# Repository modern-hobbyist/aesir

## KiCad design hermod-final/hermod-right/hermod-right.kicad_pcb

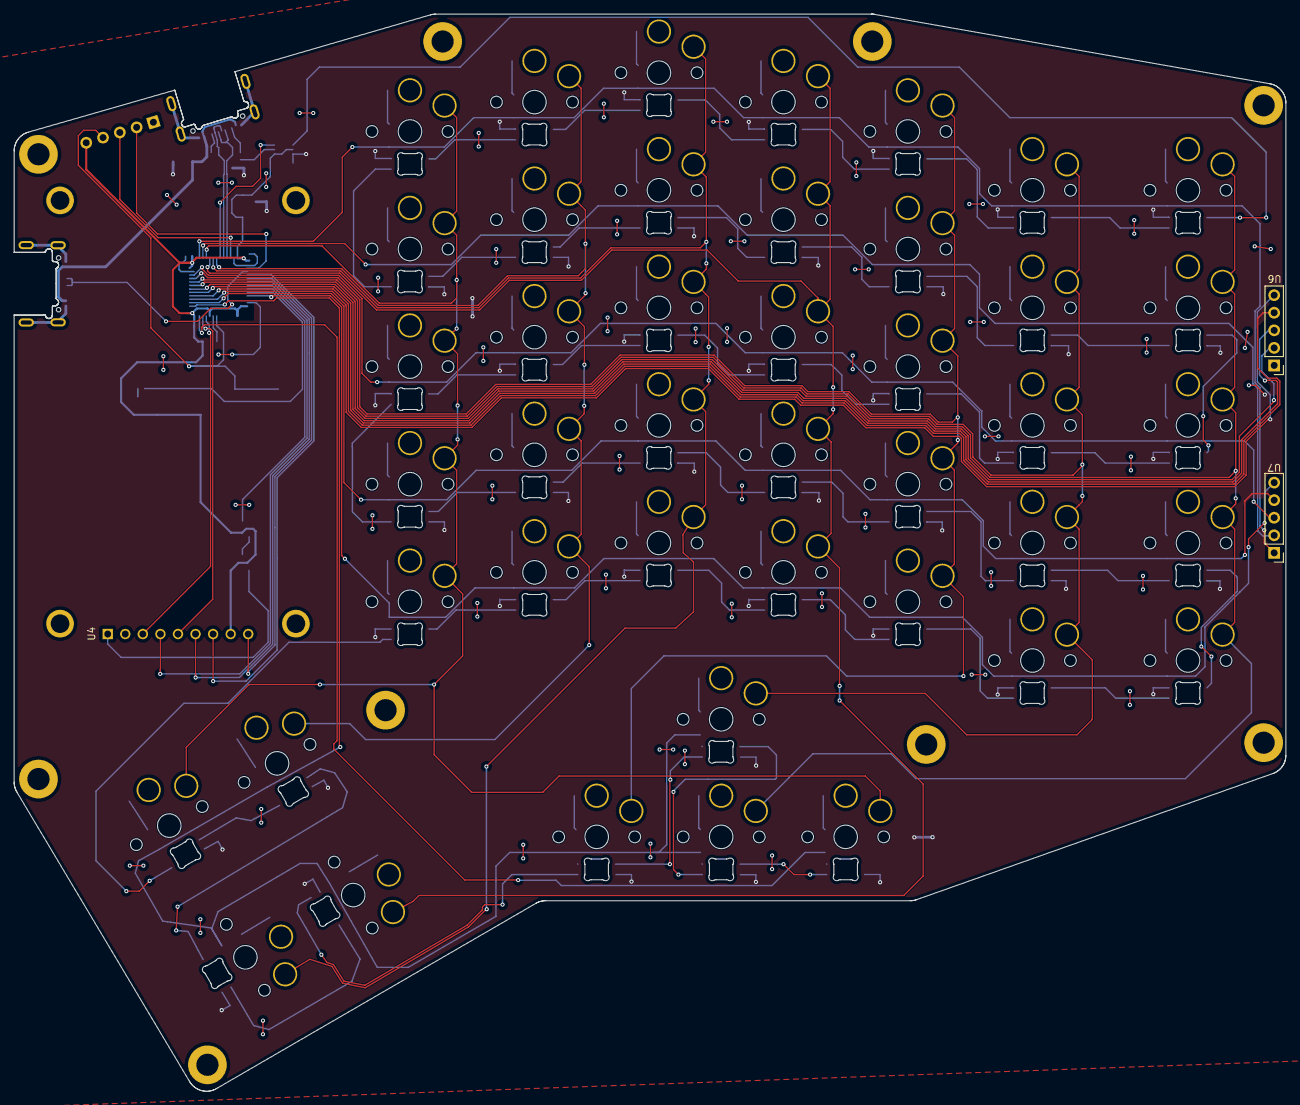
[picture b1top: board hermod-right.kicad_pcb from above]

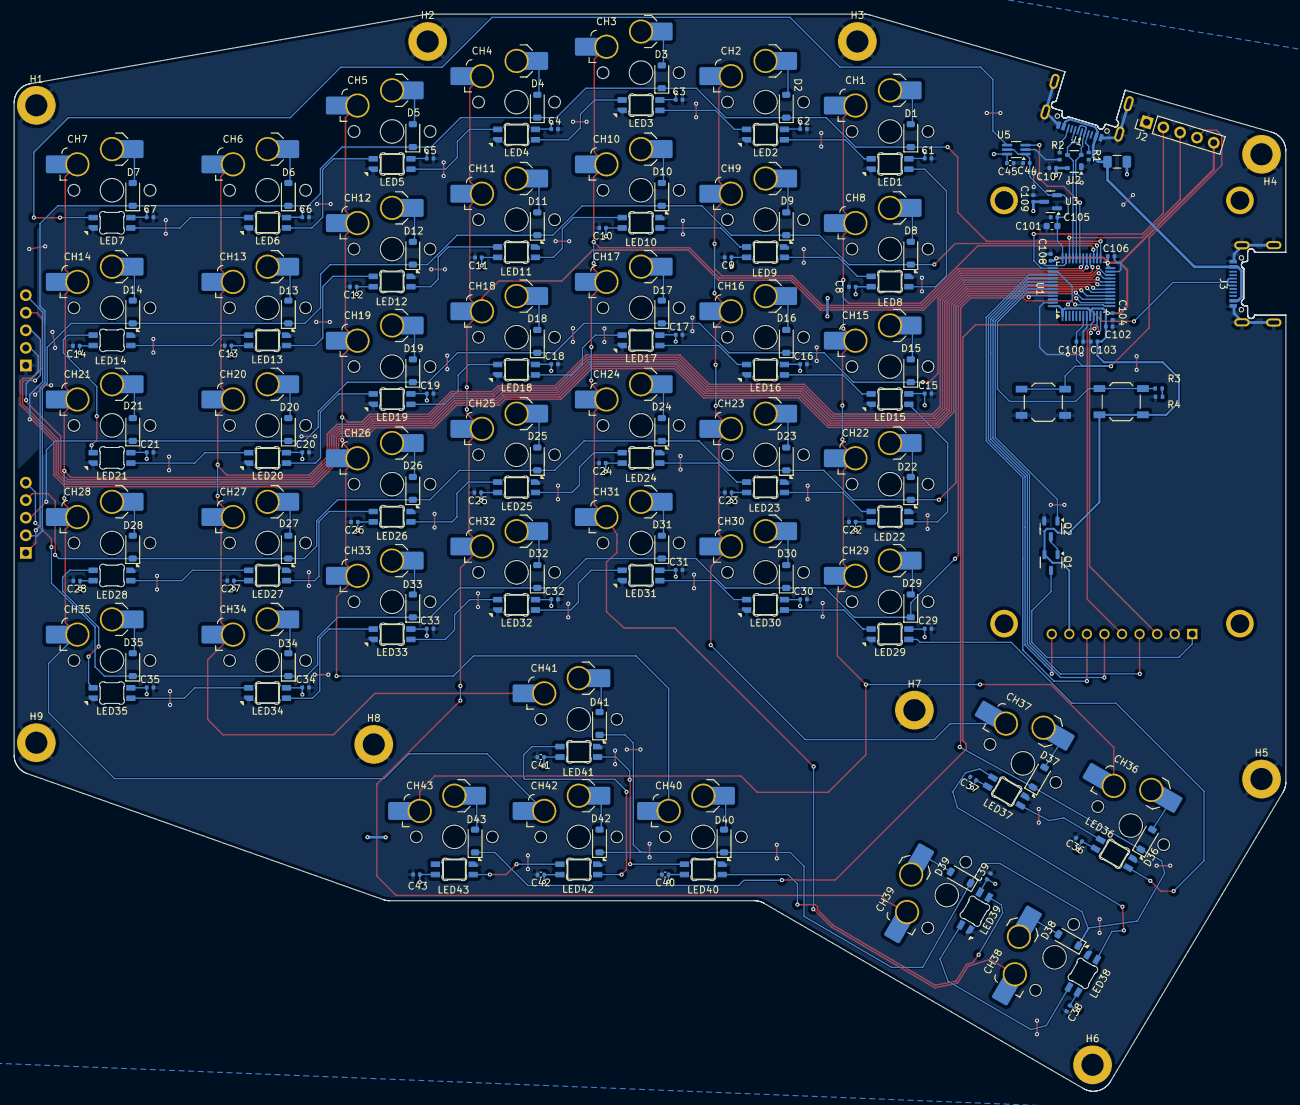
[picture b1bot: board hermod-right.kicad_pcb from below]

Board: 2 copper layers, 183.9 x 155.8 mm, 212 parts (209 on the bottom side), 128 nets.

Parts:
BOOT1: SW_SPST; SW_SPST_TL3342
C1, C2, C3, C4, C5, C6, C7, C8, C9, C10, C11, C12, C13, C14, C15, C16, C17, C18, C19, C20, C21, C22, C23, C24, C25, C26, C27, C28, C29, C30, C31, C32, C33, C34, C35, C36, C37, C38, C39, C40, C41, C42, C43, C44, C45: 0.1uF; C_0402_1005Metric
C100, C102, C103, C104, C105, C106, C109: 100nF; C_0402_1005Metric
C101: 10uF; C_0603_1608Metric
C107, C108: 1uF; C_0402_1005Metric
CH1, CH2, CH3, CH4, CH5, CH6, CH8, CH9, CH10, CH11, CH12, CH13, CH15, CH16, CH17, CH18, CH19, CH20, CH22, CH23, CH24, CH25, CH26, CH27, CH29, CH30, CH31, CH32, CH33, CH34, CH36, CH37, CH40, CH41, CH42, CH43: choc_v1_SW_HS; SW_choc_v1_HS_CPG135001S30_1u
CH7, CH14, CH21, CH28, CH35, CH38, CH39: choc_v1_SW_HS; SW_choc_v1_HS_CPG135001S30_1.5u
D1, D2, D3, D4, D5, D6, D7, D8, D9, D10, D11, D12, D13, D14, D15, D16, D17, D18, D19, D20, D21, D22, D23, D24, D25, D26, D27, D28, D29, D30, D31, D32, D33, D34, D35, D36, D37, D38, D39, D40, D41, D42, D43: D; D_SOD-123
F1: 500mA; Fuse_1206_3216Metric
H1, H2, H3, H4, H5, H6, H7, H8, H9: MountingHole_Pad; MountingHole_3.2mm_M3_DIN965_Pad
J1, J3: USB_C_Receptacle_USB2.0; USB_C_Receptacle_HRO_TYPE-C-31-M-14
J2: Conn_01x05; PinHeader_1x05_P2.54mm_Vertical
LED1, LED2, LED3, LED4, LED5, LED6, LED7, LED8, LED9, LED10, LED11, LED12, LED13, LED14, LED15, LED16, LED17, LED18, LED19, LED20, LED21, LED22, LED23, LED24, LED25, LED26, LED27, LED28, LED29, LED30, LED31, LED32, LED33, LED34, LED35, LED36, LED37, LED38, LED39, LED40, LED41, LED42, LED43: choc_SK6812MINI-E; LED_choc_6028R
Q1: AO3401A; SOT-23-3
Q2: MMUN2233LT1G; SOT-23-3
R1, R2, R3, R4: 5.1k; R_0402_1005Metric
RST1: SW_SPST; SW_SPST_TL3342
U1: STM32F072CBT6; LQFP-48_7x7mm_P0.5mm
U2: PRTR5V0U2X; SOT-143
U3: XC6206PxxxMR-Regulator_Linear; SOT-23
U4: CR2013-MI2120
U5: TXB0101; SOT-363_SC-70-6_Handsoldering
U6, U7: Pogo_2.54mm_5p

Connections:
+3V3: BOOT1.1 (A), C44.2, C101.1, C102.1, C103.1, C104.1, C105.1, C106.1, C108.1, J2.5, Q1.2 (S), U1.1 (VBAT), U1.9 (VDDA), U1.24 (VDD), U1.36 (VDDIO2), U1.48 (VDD), U3.2 (VO), U4.8 (LED), U5.1 (VCCA), U5.5 (OE)
+5V: C1.1, C2.1, C3.1, C4.1, C5.1, C6.1, C7.1, C8.1, C9.1, C10.1, C11.1, C12.1, C13.1, C14.1, C15.1, C16.1, C17.1, C18.1, C19.1, C20.1, C21.1, C22.1, C23.1, C24.1, C25.1, C26.1, C27.1, C28.1, C29.1, C30.1, C31.1, C32.1, C33.1, C34.1, C35.1, C36.1, C37.1, C38.1, C39.1, C40.1, C41.1, C42.1, C43.1, C45.1, C107.1, C109.1, F1.2, LED1.1 (VDD), LED2.1 (VDD), LED3.1 (VDD), LED4.1 (VDD), LED5.1 (VDD), LED6.1 (VDD), LED7.1 (VDD), LED8.1 (VDD), LED9.1 (VDD), LED10.1 (VDD), LED11.1 (VDD), LED12.1 (VDD), LED13.1 (VDD), LED14.1 (VDD), LED15.1 (VDD), LED16.1 (VDD), LED17.1 (VDD), LED18.1 (VDD), LED19.1 (VDD), LED20.1 (VDD), LED21.1 (VDD), LED22.1 (VDD), LED23.1 (VDD), LED24.1 (VDD), LED25.1 (VDD), LED26.1 (VDD), LED27.1 (VDD), LED28.1 (VDD), LED29.1 (VDD), LED30.1 (VDD), LED31.1 (VDD), LED32.1 (VDD), LED33.1 (VDD), LED34.1 (VDD), LED35.1 (VDD), LED36.1 (VDD), LED37.1 (VDD), LED38.1 (VDD), LED39.1 (VDD), LED40.1 (VDD), LED41.1 (VDD), LED42.1 (VDD), LED43.1 (VDD), U2.4 (VCC), U3.3 (VI), U5.6 (VCCB)
BOOT0: BOOT1.2 (B), R3.1, U1.44 (BOOT0)
D+: J1.A6 (D+), J1.B6 (D+), U1.33 (PA12), U2.3 (I/O2)
D-: J1.A7 (D-), J1.B7 (D-), U1.32 (PA11), U2.2 (I/O1)
DOut1: LED1.2 (DOUT), LED8.3 (DIN)
DOut2: LED14.2 (DOUT), LED21.3 (DIN)
DOut3: LED15.2 (DOUT), LED22.3 (DIN)
DOut4: LED28.2 (DOUT), LED35.3 (DIN)
DOut5: LED29.2 (DOUT), LED36.3 (DIN)
GND: C1.2, C2.2, C3.2, C4.2, C5.2, C6.2, C7.2, C8.2, C9.2, C10.2, C11.2, C12.2, C13.2, C14.2, C15.2, C16.2, C17.2, C18.2, C19.2, C20.2, C21.2, C22.2, C23.2, C24.2, C25.2, C26.2, C27.2, C28.2, C29.2, C30.2, C31.2, C32.2, C33.2, C34.2, C35.2, C36.2, C37.2, C38.2, C39.2, C40.2, C41.2, C42.2, C43.2, C44.1, C45.2, C100.2, C101.2, C102.2, C103.2, C104.2, C105.2, C106.2, C107.2, C108.2, C109.2, H1.1, H2.1, H3.1, H4.1, H5.1, H6.1, H7.1, H8.1, H9.1, J1.A1 (GND), J1.A12 (GND), J1.B1 (GND), J1.B12 (GND), J1.S1 (SHIELD), J2.1, J3.A1 (GND), J3.A12 (GND), J3.B1 (GND), J3.B12 (GND), J3.S1 (SHIELD), LED1.4 (VSS), LED2.4 (VSS), LED3.4 (VSS), LED4.4 (VSS), LED5.4 (VSS), LED6.4 (VSS), LED7.4 (VSS), LED8.4 (VSS), LED9.4 (VSS), LED10.4 (VSS), LED11.4 (VSS), LED12.4 (VSS), LED13.4 (VSS), LED14.4 (VSS), LED15.4 (VSS), LED16.4 (VSS), LED17.4 (VSS), LED18.4 (VSS), LED19.4 (VSS), LED20.4 (VSS), LED21.4 (VSS), LED22.4 (VSS), LED23.4 (VSS), LED24.4 (VSS), LED25.4 (VSS), LED26.4 (VSS), LED27.4 (VSS), LED28.4 (VSS), LED29.4 (VSS), LED30.4 (VSS), LED31.4 (VSS), LED32.4 (VSS), LED33.4 (VSS), LED34.4 (VSS), LED35.4 (VSS), LED36.4 (VSS), LED37.4 (VSS), LED38.4 (VSS), LED39.4 (VSS), LED40.4 (VSS), LED41.4 (VSS), LED42.4 (VSS), LED43.4 (VSS), Q2.2 (E), R1.1, R2.2, R4.2, RST1.2 (B), U1.8 (VSSA), U1.23 (VSS), U1.35 (VSS), U1.47 (VSS), U2.1 (GND), U3.1 (GND), U4.2 (GND), U5.2 (GND), U6.1
LCD_CS: U1.10 (PA0), U4.3 (~CS)
LCD_DC: U1.11 (PA1), U4.5 (D/~C)
LCD_EN: Q2.1 (B), U1.43 (PB7)
LCD_MISO: U1.40 (PB4), U4.9 (MISO)
LCD_MOSI: U1.41 (PB5), U4.6 (MOSI)
LCD_PWR: Q1.3 (D), U4.1 (VCC)
LCD_RST: U1.42 (PB6), U4.4 (RESET)
LCD_SCK: U1.39 (PB3), U4.7 (SCK)
NRST: C100.1, J2.4, RST1.1 (A), U1.7 (NRST)
unnamed: CH1.2, D1.2 (A)
unnamed: CH2.2, D2.2 (A)
unnamed: CH3.2, D3.2 (A)
unnamed: CH4.2, D4.2 (A)
unnamed: CH5.2, D5.2 (A)
unnamed: CH6.2, D6.2 (A)
unnamed: CH7.2, D7.2 (A)
unnamed: CH8.2, D8.2 (A)
unnamed: CH9.2, D9.2 (A)
unnamed: CH10.2, D10.2 (A)
unnamed: CH11.2, D11.2 (A)
unnamed: CH12.2, D12.2 (A)
unnamed: CH13.2, D13.2 (A)
unnamed: CH14.2, D14.2 (A)
unnamed: CH15.2, D15.2 (A)
unnamed: CH16.2, D16.2 (A)
unnamed: CH17.2, D17.2 (A)
unnamed: CH18.2, D18.2 (A)
unnamed: CH19.2, D19.2 (A)
unnamed: CH20.2, D20.2 (A)
unnamed: CH21.2, D21.2 (A)
unnamed: CH22.2, D22.2 (A)
unnamed: CH23.2, D23.2 (A)
unnamed: CH24.2, D24.2 (A)
unnamed: CH25.2, D25.2 (A)
unnamed: CH26.2, D26.2 (A)
unnamed: CH27.2, D27.2 (A)
unnamed: CH28.2, D28.2 (A)
unnamed: CH29.2, D29.2 (A)
unnamed: CH30.2, D30.2 (A)
unnamed: CH31.2, D31.2 (A)
unnamed: CH32.2, D32.2 (A)
unnamed: CH33.2, D33.2 (A)
unnamed: CH34.2, D34.2 (A)
unnamed: CH35.2, D35.2 (A)
unnamed: CH36.2, D36.2 (A)
unnamed: CH37.2, D37.2 (A)
unnamed: CH38.2, D38.2 (A)
unnamed: CH39.2, D39.2 (A)
unnamed: CH40.2, D40.2 (A)
unnamed: CH41.2, D41.2 (A)
unnamed: CH42.2, D42.2 (A)
unnamed: CH43.2, D43.2 (A)
unnamed: J1.A5 (CC1), R1.2
unnamed: J1.B5 (CC2), R2.1
unnamed: LED1.3 (DIN), LED2.2 (DOUT)
unnamed: LED2.3 (DIN), LED3.2 (DOUT)
unnamed: LED3.3 (DIN), LED4.2 (DOUT)
unnamed: LED4.3 (DIN), LED5.2 (DOUT)
unnamed: LED5.3 (DIN), LED6.2 (DOUT)
unnamed: LED6.3 (DIN), LED7.2 (DOUT)
unnamed: LED8.2 (DOUT), LED9.3 (DIN)
unnamed: LED9.2 (DOUT), LED10.3 (DIN)
unnamed: LED10.2 (DOUT), LED11.3 (DIN)
unnamed: LED11.2 (DOUT), LED12.3 (DIN)
unnamed: LED12.2 (DOUT), LED13.3 (DIN)
unnamed: LED13.2 (DOUT), LED14.3 (DIN)
unnamed: LED15.3 (DIN), LED16.2 (DOUT)
unnamed: LED16.3 (DIN), LED17.2 (DOUT)
unnamed: LED17.3 (DIN), LED18.2 (DOUT)
unnamed: LED18.3 (DIN), LED19.2 (DOUT)
unnamed: LED19.3 (DIN), LED20.2 (DOUT)
unnamed: LED20.3 (DIN), LED21.2 (DOUT)
unnamed: LED22.2 (DOUT), LED23.3 (DIN)
unnamed: LED23.2 (DOUT), LED24.3 (DIN)
unnamed: LED24.2 (DOUT), LED25.3 (DIN)
unnamed: LED25.2 (DOUT), LED26.3 (DIN)
unnamed: LED26.2 (DOUT), LED27.3 (DIN)
unnamed: LED27.2 (DOUT), LED28.3 (DIN)
unnamed: LED29.3 (DIN), LED30.2 (DOUT)
unnamed: LED30.3 (DIN), LED31.2 (DOUT)
unnamed: LED31.3 (DIN), LED32.2 (DOUT)
unnamed: LED32.3 (DIN), LED33.2 (DOUT)
unnamed: LED33.3 (DIN), LED34.2 (DOUT)
unnamed: LED34.3 (DIN), LED35.2 (DOUT)
unnamed: LED36.2 (DOUT), LED37.3 (DIN)
unnamed: LED37.2 (DOUT), LED38.3 (DIN)
unnamed: LED38.2 (DOUT), LED39.3 (DIN)
unnamed: LED39.2 (DOUT), LED40.3 (DIN)
unnamed: LED40.2 (DOUT), LED41.3 (DIN)
unnamed: LED41.2 (DOUT), LED42.3 (DIN)
unnamed: LED42.2 (DOUT), LED43.3 (DIN)
unnamed: Q1.1 (G), Q2.3 (C)
unnamed: R3.2, R4.1
RGB3.3: U1.31 (PA10), U5.3 (A)
RGB5v: LED7.3 (DIN), U5.4 (B)
SWCLK: J2.2, U1.37 (PA14)
SWD: J2.3, U1.34 (PA13)
SplitSerial: J3.A6 (D+), J3.B6 (D+), U1.38 (PA15)
VBUS: F1.1, J1.A4 (VBUS), J1.A9 (VBUS), J1.B4 (VBUS), J1.B9 (VBUS), J3.A4 (VBUS), J3.A9 (VBUS), J3.B4 (VBUS), J3.B9 (VBUS)
col0: CH1.1, CH8.1, CH15.1, CH22.1, CH29.1, CH36.1, CH43.1, U1.27 (PB14)
col1: CH2.1, CH9.1, CH16.1, CH23.1, CH30.1, CH37.1, U1.30 (PA9)
col2: CH3.1, CH10.1, CH17.1, CH24.1, CH31.1, CH38.1, U1.29 (PA8)
col3: CH4.1, CH11.1, CH18.1, CH25.1, CH32.1, CH39.1, U1.28 (PB15)
col4: CH5.1, CH12.1, CH19.1, CH26.1, CH33.1, CH40.1, U1.21 (PB10)
col5: CH6.1, CH13.1, CH20.1, CH27.1, CH34.1, CH41.1, U1.20 (PB2)
col6: CH7.1, CH14.1, CH21.1, CH28.1, CH35.1, CH42.1, U1.19 (PB1)
col7: U1.15 (PA5), U6.5
col8: U1.16 (PA6), U6.4
col9: U1.17 (PA7), U6.3
col10: U1.18 (PB0), U6.2
row0: D1.1 (K), D2.1 (K), D3.1 (K), D4.1 (K), D5.1 (K), D6.1 (K), D7.1 (K), U1.25 (PB12), U7.1
row1: D8.1 (K), D9.1 (K), D10.1 (K), D11.1 (K), D12.1 (K), D13.1 (K), D14.1 (K), U1.26 (PB13), U7.2
row2: D15.1 (K), D16.1 (K), D17.1 (K), D18.1 (K), D19.1 (K), D20.1 (K), D21.1 (K), U1.22 (PB11), U7.3
row3: D22.1 (K), D23.1 (K), D24.1 (K), D25.1 (K), D26.1 (K), D27.1 (K), D28.1 (K), U1.14 (PA4), U7.4
row4: D29.1 (K), D30.1 (K), D31.1 (K), D32.1 (K), D33.1 (K), D34.1 (K), D35.1 (K), U1.45 (PB8), U7.5
row5: D36.1 (K), D37.1 (K), D38.1 (K), D39.1 (K), D40.1 (K), D41.1 (K), D42.1 (K), U1.13 (PA3)
row6: D43.1 (K), U1.12 (PA2)
